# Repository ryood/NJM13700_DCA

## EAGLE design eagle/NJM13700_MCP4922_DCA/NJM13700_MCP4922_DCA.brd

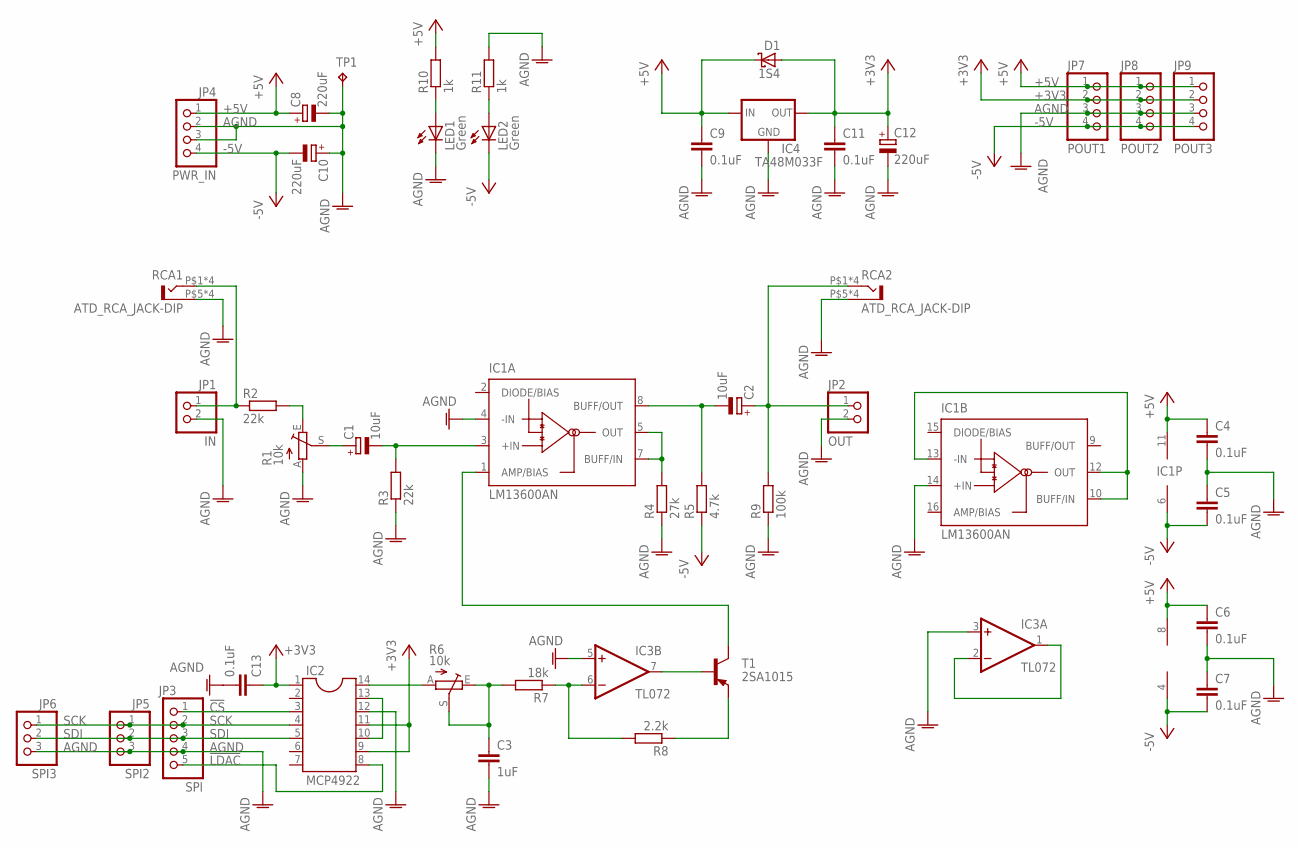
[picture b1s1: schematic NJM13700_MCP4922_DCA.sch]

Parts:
C1: 10uF; E5-6
C2: 10uF; E2,5-6
C3: 1uF; C050-024X044
C4, C5, C6, C7, C9, C11, C13: 0.1uF; C025-024X044
C8, C10, C12: 220uF; E5-8,5
D1: 1S4; DO35-7
IC1: LM13600AN; DIL16
IC2: MCP4922; DIL14
IC3: TL072; DIL08
IC4: TA48M033F; 78XXS
JP1: IN; 1X02
JP2: OUT; 1X02
JP3: SPI; 1X05
JP4: PWR_IN; 1X04
JP5: SPI2; 1X03
JP6: SPI3; 1X03
JP7: POUT1; 1X04
JP8: POUT2; 1X04
JP9: POUT3; 1X04
LED1, LED2: Green; LED3MM
R1, R6: 10k; B25P
R2, R3: 22k; 0207/7
R4: 27k; 0207/7
R5: 4.7k; 0207/7
R7: 18k; 0207/7
R8: 2.2k; 0207/7
R9: 100k; 0207/7
R10, R11: 1k; 0207/7
RCA1, RCA2: ATD_RCA_JACK-DIP; ATD_RCA_JACK_DIP
T1: 2SA1015; TO92-ECB
TP1: TPPAD1-13; P1-13

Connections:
!CS: IC2.3, JP3.1
!LDAC: IC2.8, JP3.5
+3V3: C11.1, C12.+, C13.2, D1.A, IC2.1, IC2.9, IC2.11, IC4.OUT, JP7.2, JP8.2, JP9.2
+5V: C4.1, C6.1, C8.+, C9.1, D1.C, IC1.11 (V+), IC3.8 (V+), IC4.IN, JP4.1, JP7.1, JP8.1, JP9.1, R10.2
-5V: C5.2, C7.2, C10.-, IC1.6 (V-), IC3.4 (V-), JP4.4, JP7.4, JP8.4, JP9.4, LED2.K (C), R5.1
AGND: C3.2, C4.2, C5.1, C6.2, C7.1, C8.-, C9.2, C10.+, C11.2, C12.-, C13.1, IC1.4 (-IN), IC1.14 (+IN), IC2.12, IC3.3 (+IN), IC3.5 (+IN), IC4.GND, JP1.2, JP2.2, JP3.4, JP4.2, JP4.3, JP5.3, JP6.3, JP7.3, JP8.3, JP9.3, LED1.K (C), R1.A, R3.1, R4.1, R9.1, R11.2, RCA1.P$5 (S), RCA1.P$6 (S), RCA1.P$7 (S), RCA1.P$8 (S), RCA2.P$5 (S), RCA2.P$6 (S), RCA2.P$7 (S), RCA2.P$8 (S), TP1.TP
unnamed: JP1.1, R2.1, RCA1.P$1 (T), RCA1.P$2 (T), RCA1.P$3 (T), RCA1.P$4 (T)
unnamed: R1.E, R2.2
unnamed: C1.+, R1.S
unnamed: C1.-, IC1.3 (+IN), R3.2
unnamed: IC1.5 (OUT), IC1.7 (BUFF/IN), R4.2
unnamed: C2.-, IC1.8 (BUFF/OUT), R5.2
unnamed: IC2.14, R6.A
unnamed: C3.1, R6.E, R6.S, R7.2
unnamed: IC3.7 (OUT), T1.B
unnamed: IC3.6 (-IN), R7.1, R8.2
unnamed: R8.1, T1.E
unnamed: IC1.1 (AMP/BIAS), T1.C
unnamed: IC2.10, IC2.13
unnamed: IC1.10 (BUFF/IN), IC1.12 (OUT), IC1.13 (-IN)
unnamed: LED2.A, R11.1
unnamed: IC3.1 (OUT), IC3.2 (-IN)
unnamed: C2.+, JP2.1, R9.2, RCA2.P$1 (T), RCA2.P$2 (T), RCA2.P$3 (T), RCA2.P$4 (T)
unnamed: LED1.A, R10.1
SCK: IC2.4, JP3.2, JP5.1, JP6.1
SDI: IC2.5, JP3.3, JP5.2, JP6.2

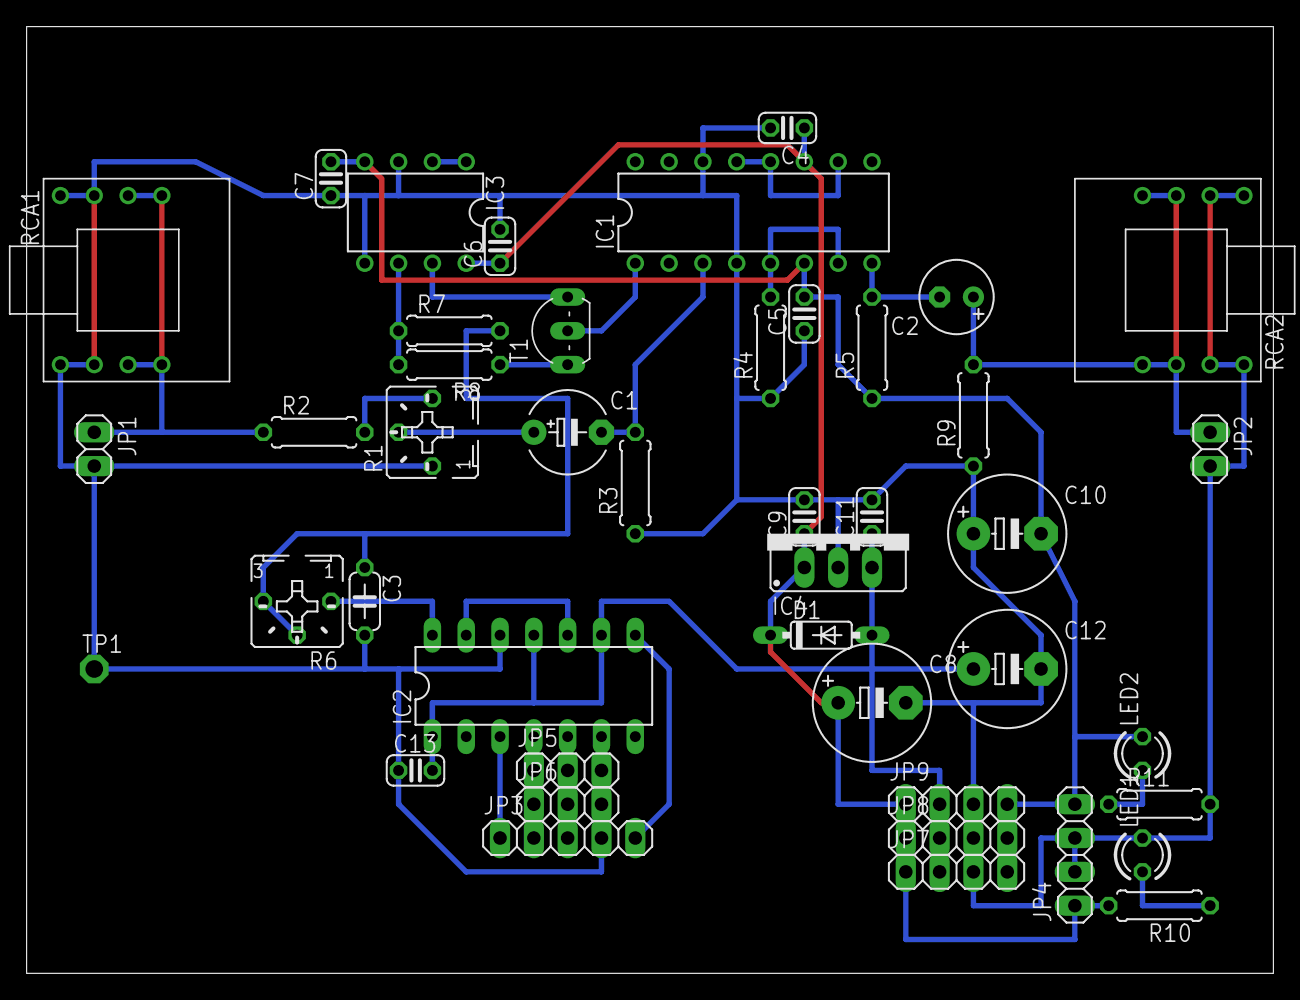
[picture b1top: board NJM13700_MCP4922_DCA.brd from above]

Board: 2 copper layers, 93.7 x 71.1 mm, 44 parts (0 on the bottom side), 26 nets.

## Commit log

2016-07-23 change parameters
2016-07-25 Add: Board design
2016-07-25 updated schematic & board designe
2016-07-25 add LED
2016-07-25 IC1、IC2の電源ラインのGNDへの接続を消去
2016-07-27 Update: board design
2016-07-29 テスト表追加
2016-07-29 画像ファイルを追加
